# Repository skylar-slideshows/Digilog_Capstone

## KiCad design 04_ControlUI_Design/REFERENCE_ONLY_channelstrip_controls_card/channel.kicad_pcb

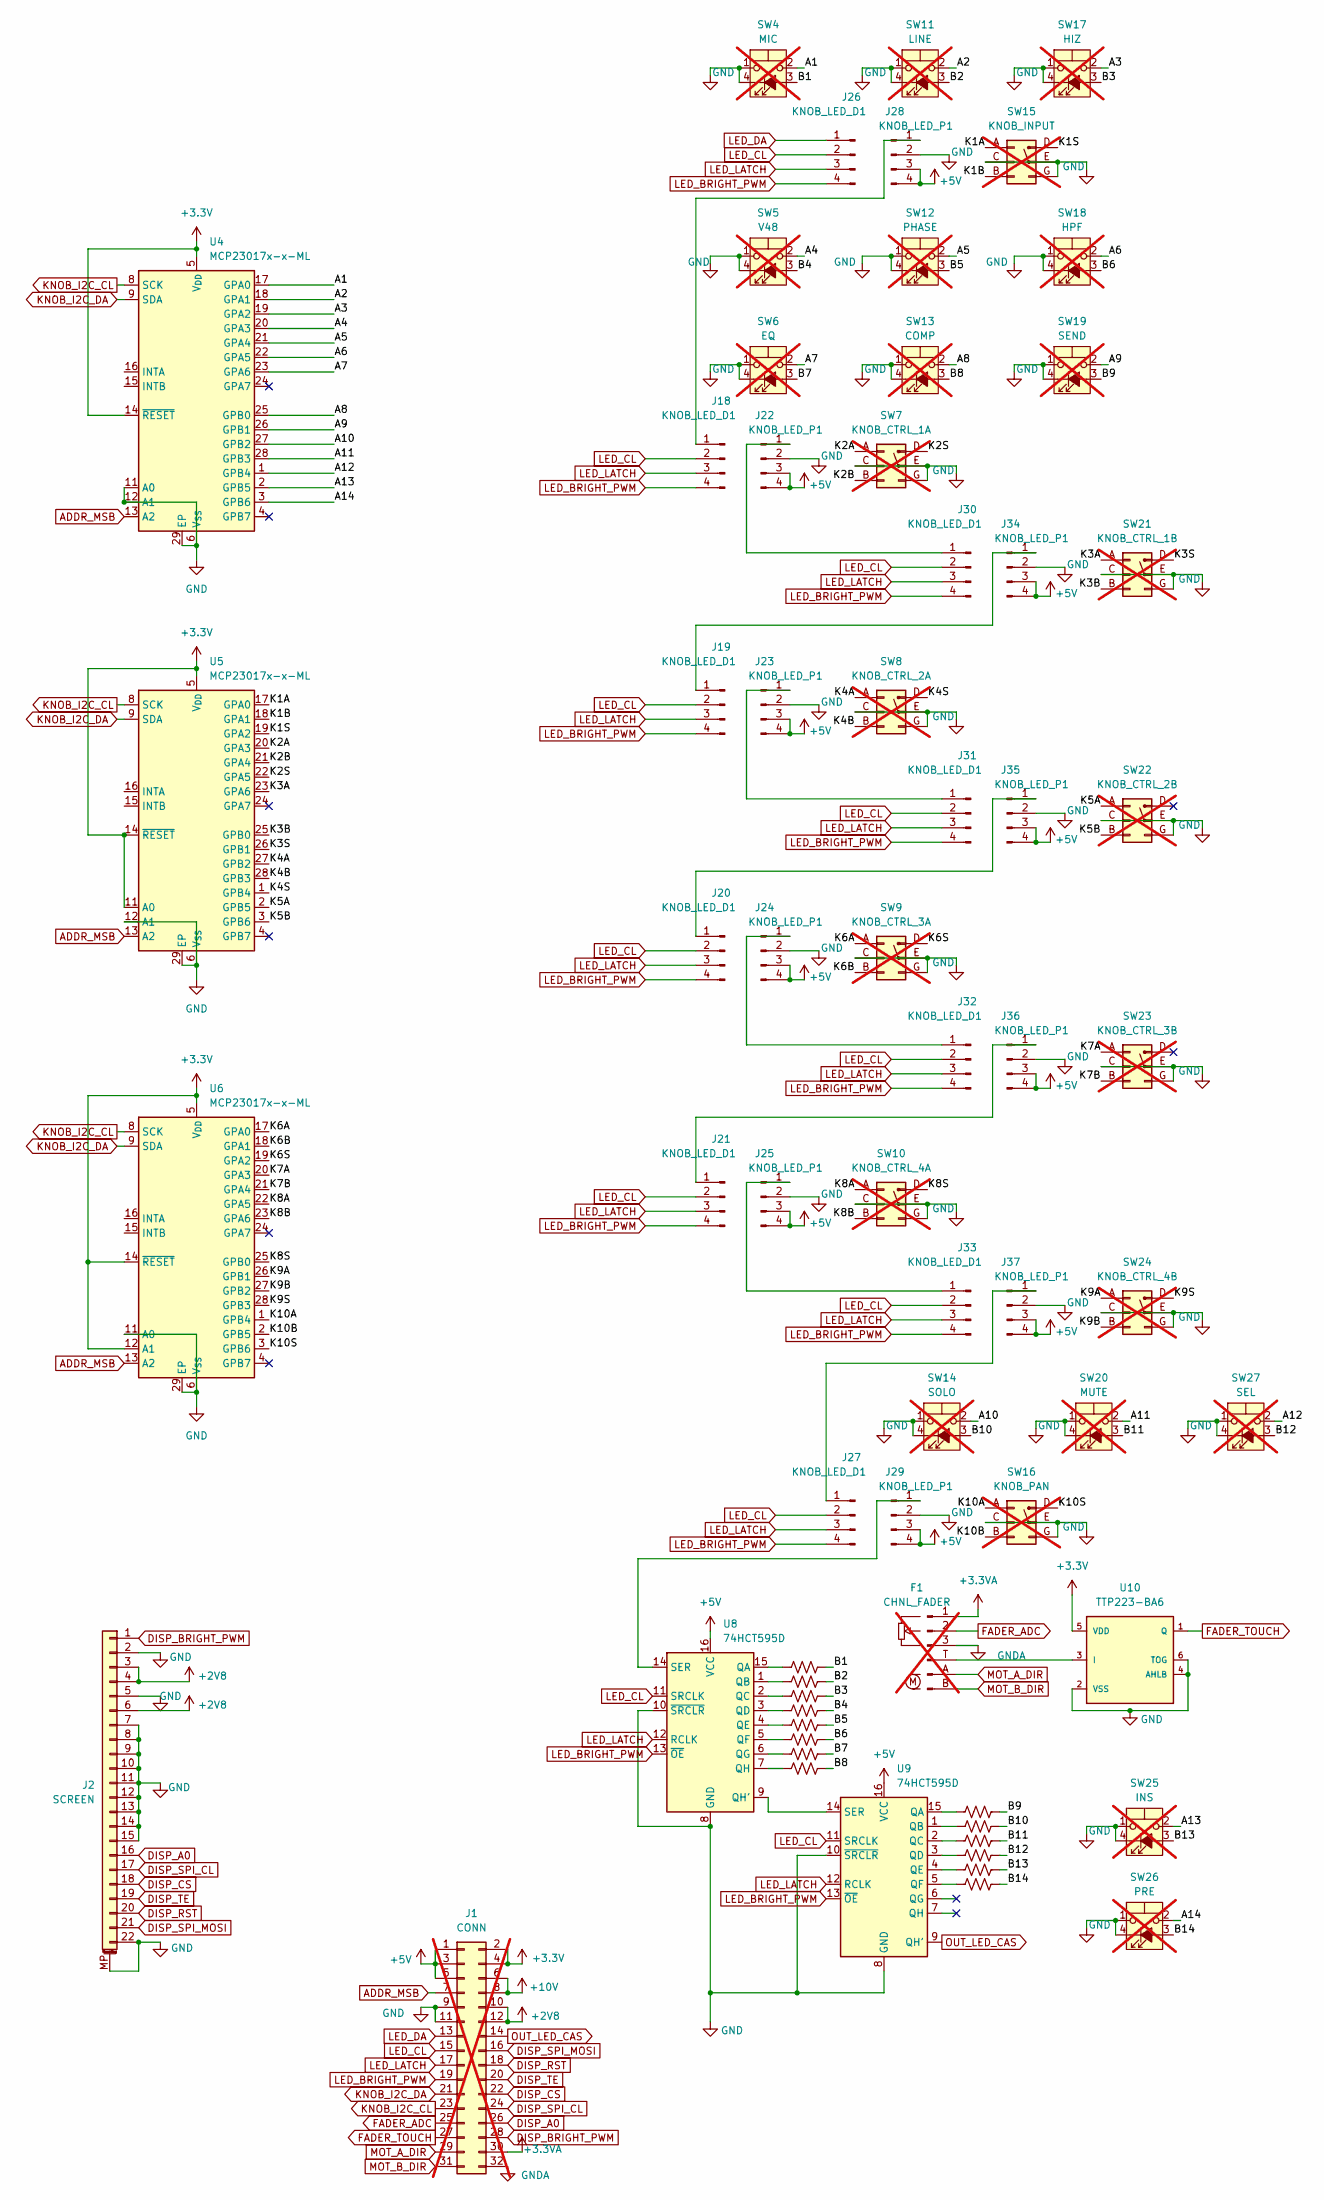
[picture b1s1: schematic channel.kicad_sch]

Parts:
F1: CHNL_FADER; TRIM_RSA0N11M9A07; not fitted
J1: CONN; PinHeader_2x16_P2.54mm_Vertical; not fitted
J2: SCREEN; TE_2-1734839-2_1x22-1MP_P0.5mm_Horizontal; LCSC C22435644
J18, J19, J20, J21, J26, J27, J30, J31, J32, J33: KNOB_LED_D1; PinSocket_1x04_P2.54mm_Vertical; LCSC C2718488
J22, J23, J24, J25, J28, J29, J34, J35, J36, J37: KNOB_LED_P1; PinSocket_1x04_P2.54mm_Vertical; LCSC C2718488
R1, R2, R3, R4, R5, R6, R7, R8, R9, R10, R11, R12, R13, R14: 330; R_0603_1608Metric; LCSC C25231
SW4: MIC; CFPB-1CC-4W6; not fitted
SW5: V48; CFPB-1CC-4W6; not fitted
SW6: EQ; CFPB-1CC-4W6; not fitted
SW7: KNOB_CTRL_1A; EC11J0924411; not fitted
SW8: KNOB_CTRL_2A; EC11J0924411; not fitted
SW9: KNOB_CTRL_3A; EC11J0924411; not fitted
SW10: KNOB_CTRL_4A; EC11J0924411; not fitted
SW11: LINE; CFPB-1CC-4W6; not fitted
SW12: PHASE; CFPB-1CC-4W6; not fitted
SW13: COMP; CFPB-1CC-4W6; not fitted
SW14: SOLO; CFPB-1CC-4W6; not fitted
SW15: KNOB_INPUT; EC11J0924411; not fitted
SW16: KNOB_PAN; EC11J0924411; not fitted
SW17: HIZ; CFPB-1CC-4W6; not fitted
SW18: HPF; CFPB-1CC-4W6; not fitted
SW19: SEND; CFPB-1CC-4W6; not fitted
SW20: MUTE; CFPB-1CC-4W6; not fitted
SW21: KNOB_CTRL_1B; EC11J0924411; not fitted
SW22: KNOB_CTRL_2B; EC11J0924411; not fitted
SW23: KNOB_CTRL_3B; EC11J0924411; not fitted
SW24: KNOB_CTRL_4B; EC11J0924411; not fitted
SW25: INS; CFPB-1CC-4W6; not fitted
SW26: PRE; CFPB-1CC-4W6; not fitted
SW27: SEL; CFPB-1CC-4W6; not fitted
U4, U5, U6: MCP23017x-x-ML; QFN-28-1EP_6x6mm_P0.65mm_EP4.25x4.25mm_ThermalVias; LCSC C629439
U8, U9: 74HCT595D; JEITA_SOIC-16_3.9x9.9mm_P1.27mm; LCSC C52140404
U10: TTP223-BA6; SOT-23-6; LCSC C42422127

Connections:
+2V8: J1.10, J1.12, J2.3, J2.4, J2.6
+3.3V: J1.2, J1.4, U4.5 (V_{DD}), U4.14 (~RESET), U5.5 (V_{DD}), U5.11 (A0), U5.14 (~RESET), U6.5 (V_{DD}), U6.12 (A1), U6.14 (~RESET), U10.5 (VDD)
+3.3VA: F1.1, J1.30
+5V: J1.1, J1.3, J1.5, J22.3, J22.4, J23.3, J23.4, J24.3, J24.4, J25.3, J25.4, J28.3, J28.4, J29.3, J29.4, J34.3, J34.4, J35.3, J35.4, J36.3, J36.4, J37.3, J37.4, U8.16 (VCC), U9.16 (VCC)
+10V: J1.6, J1.8
/A1: SW4.2, U4.17 (GPA0)
/A2: SW11.2, U4.18 (GPA1)
/A3: SW17.2, U4.19 (GPA2)
/A4: SW5.2, U4.20 (GPA3)
/A5: SW12.2, U4.21 (GPA4)
/A6: SW18.2, U4.22 (GPA5)
/A7: SW6.2, U4.23 (GPA6)
/A8: SW13.2, U4.25 (GPB0)
/A9: SW19.2, U4.26 (GPB1)
/A10: SW14.2, U4.27 (GPB2)
/A11: SW20.2, U4.28 (GPB3)
/A12: SW27.2, U4.1 (GPB4)
/A13: SW25.2, U4.2 (GPB5)
/A14: SW26.2, U4.3 (GPB6)
/B1: R1.2, SW4.3 (A)
/B2: R2.2, SW11.3 (A)
/B3: R3.2, SW17.3 (A)
/B4: R4.2, SW5.3 (A)
/B5: R5.2, SW12.3 (A)
/B6: R6.2, SW18.3 (A)
/B7: R7.2, SW6.3 (A)
/B8: R8.2, SW13.3 (A)
/B9: R9.2, SW19.3 (A)
/B10: R10.2, SW14.3 (A)
/B11: R11.2, SW20.3 (A)
/B12: R12.2, SW27.3 (A)
/B13: R13.2, SW25.3 (A)
/B14: R14.2, SW26.3 (A)
/K1A: SW15.A (Pin_1), U5.17 (GPA0)
/K1B: SW15.B (Pin_3), U5.18 (GPA1)
/K1S: SW15.D (Pin_4), U5.19 (GPA2)
/K2A: SW7.A (Pin_1), U5.20 (GPA3)
/K2B: SW7.B (Pin_3), U5.21 (GPA4)
/K2S: SW7.D (Pin_4), U5.22 (GPA5)
/K3A: SW21.A (Pin_1), U5.23 (GPA6)
/K3B: SW21.B (Pin_3), U5.25 (GPB0)
/K3S: SW21.D (Pin_4), U5.26 (GPB1)
/K4A: SW8.A (Pin_1), U5.27 (GPB2)
/K4B: SW8.B (Pin_3), U5.28 (GPB3)
/K4S: SW8.D (Pin_4), U5.1 (GPB4)
/K5A: SW22.A (Pin_1), U5.2 (GPB5)
/K5B: SW22.B (Pin_3), U5.3 (GPB6)
/K6A: SW9.A (Pin_1), U6.17 (GPA0)
/K6B: SW9.B (Pin_3), U6.18 (GPA1)
/K6S: SW9.D (Pin_4), U6.19 (GPA2)
/K7A: SW23.A (Pin_1), U6.20 (GPA3)
/K7B: SW23.B (Pin_3), U6.21 (GPA4)
/K8A: SW10.A (Pin_1), U6.22 (GPA5)
/K8B: SW10.B (Pin_3), U6.23 (GPA6)
/K8S: SW10.D (Pin_4), U6.25 (GPB0)
/K9A: SW24.A (Pin_1), U6.26 (GPB1)
/K9B: SW24.B (Pin_3), U6.27 (GPB2)
/K9S: SW24.D (Pin_4), U6.28 (GPB3)
/K10A: SW16.A (Pin_1), U6.1 (GPB4)
/K10B: SW16.B (Pin_3), U6.2 (GPB5)
/K10S: SW16.D (Pin_4), U6.3 (GPB6)
ADDR_MSB: J1.7, U4.13 (A2), U5.13 (A2), U6.13 (A2)
DISP_A0: J1.26, J2.16
DISP_BRIGHT_PWM: J1.28, J2.1
DISP_CS: J1.22, J2.18
DISP_RST: J1.18, J2.20
DISP_SPI_CL: J1.24, J2.17
DISP_SPI_MOSI: J1.16, J2.21
DISP_TE: J1.20, J2.19
FADER_ADC: F1.2, J1.25
FADER_TOUCH: J1.27, U10.1 (Q)
GND: J1.9, J1.11, J2.2, J2.5, J2.7, J2.8, J2.9, J2.10, J2.11, J2.12, J2.13, J2.14, J2.15, J2.22, J2.MP (MountPin), J22.2, J23.2, J24.2, J25.2, J28.2, J29.2, J34.2, J35.2, J36.2, J37.2, SW4.1, SW4.4 (K), SW5.1, SW5.4 (K), SW6.1, SW6.4 (K), SW7.C (Pin_2), SW7.E (Pin_5), SW7.G (Pin_6), SW8.C (Pin_2), SW8.E (Pin_5), SW8.G (Pin_6), SW9.C (Pin_2), SW9.E (Pin_5), SW9.G (Pin_6), SW10.C (Pin_2), SW10.E (Pin_5), SW10.G (Pin_6), SW11.1, SW11.4 (K), SW12.1, SW12.4 (K), SW13.1, SW13.4 (K), SW14.1, SW14.4 (K), SW15.C (Pin_2), SW15.E (Pin_5), SW15.G (Pin_6), SW16.C (Pin_2), SW16.E (Pin_5), SW16.G (Pin_6), SW17.1, SW17.4 (K), SW18.1, SW18.4 (K), SW19.1, SW19.4 (K), SW20.1, SW20.4 (K), SW21.C (Pin_2), SW21.E (Pin_5), SW21.G (Pin_6), SW22.C (Pin_2), SW22.E (Pin_5), SW22.G (Pin_6), SW23.C (Pin_2), SW23.E (Pin_5), SW23.G (Pin_6), SW24.C (Pin_2), SW24.E (Pin_5), SW24.G (Pin_6), SW25.1, SW25.4 (K), SW26.1, SW26.4 (K), SW27.1, SW27.4 (K), U4.6 (V_{SS}), U4.11 (A0), U4.12 (A1), U4.29 (EP), U5.6 (V_{SS}), U5.12 (A1), U5.29 (EP), U6.6 (V_{SS}), U6.11 (A0), U6.29 (EP), U8.8 (GND), U8.10 (~SRCLR), U9.8 (GND), U9.10 (~SRCLR), U10.2 (VSS), U10.4 (AHLB), U10.6 (TOG)
GNDA: F1.3, J1.32
KNOB_I2C_CL: J1.23, U4.8 (SCK), U5.8 (SCK), U6.8 (SCK)
KNOB_I2C_DA: J1.21, U4.9 (SDA), U5.9 (SDA), U6.9 (SDA)
LED_BRIGHT_PWM: J1.19, J18.4, J19.4, J20.4, J21.4, J26.4, J27.4, J30.4, J31.4, J32.4, J33.4, U8.13 (~OE), U9.13 (~OE)
LED_CL: J1.15, J18.2, J19.2, J20.2, J21.2, J26.2, J27.2, J30.2, J31.2, J32.2, J33.2, U8.11 (SRCLK), U9.11 (SRCLK)
LED_DA: J1.13, J26.1
LED_LATCH: J1.17, J18.3, J19.3, J20.3, J21.3, J26.3, J27.3, J30.3, J31.3, J32.3, J33.3, U8.12 (RCLK), U9.12 (RCLK)
MOT_A_DIR: F1.A (Pin_5), J1.29
MOT_B_DIR: F1.B (Pin_6), J1.31
unnamed: F1.T (Pin_4), U10.3 (I)
unnamed: J18.1, J28.1
unnamed: J19.1, J34.1
unnamed: J20.1, J35.1
unnamed: J21.1, J36.1
unnamed: J22.1, J30.1
unnamed: J23.1, J31.1
unnamed: J24.1, J32.1
unnamed: J25.1, J33.1
unnamed: J27.1, J37.1
unnamed: J29.1, U8.14 (SER)
unnamed: R1.1, U8.15 (QA)
unnamed: R2.1, U8.1 (QB)
unnamed: R3.1, U8.2 (QC)
unnamed: R4.1, U8.3 (QD)
unnamed: R5.1, U8.4 (QE)
unnamed: R6.1, U8.5 (QF)
unnamed: R7.1, U8.6 (QG)
unnamed: U8.9 (QH'), U9.14 (SER)
unnamed: R8.1, U8.7 (QH)
unnamed: R9.1, U9.15 (QA)
unnamed: R10.1, U9.1 (QB)
unnamed: R11.1, U9.2 (QC)
unnamed: R12.1, U9.3 (QD)
unnamed: R13.1, U9.4 (QE)
unnamed: R14.1, U9.5 (QF)
OUT_LED_CAS: J1.14, U9.9 (QH')

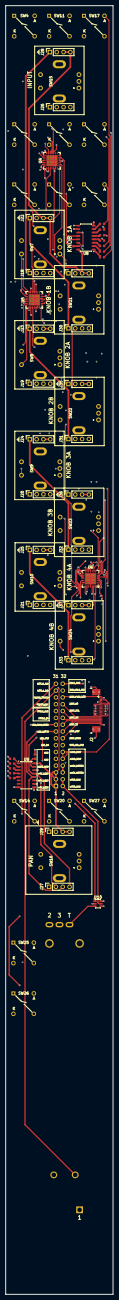
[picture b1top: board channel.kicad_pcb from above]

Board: 4 copper layers, 40.0 x 480.0 mm, 67 parts (1 on the bottom side), 108 nets.

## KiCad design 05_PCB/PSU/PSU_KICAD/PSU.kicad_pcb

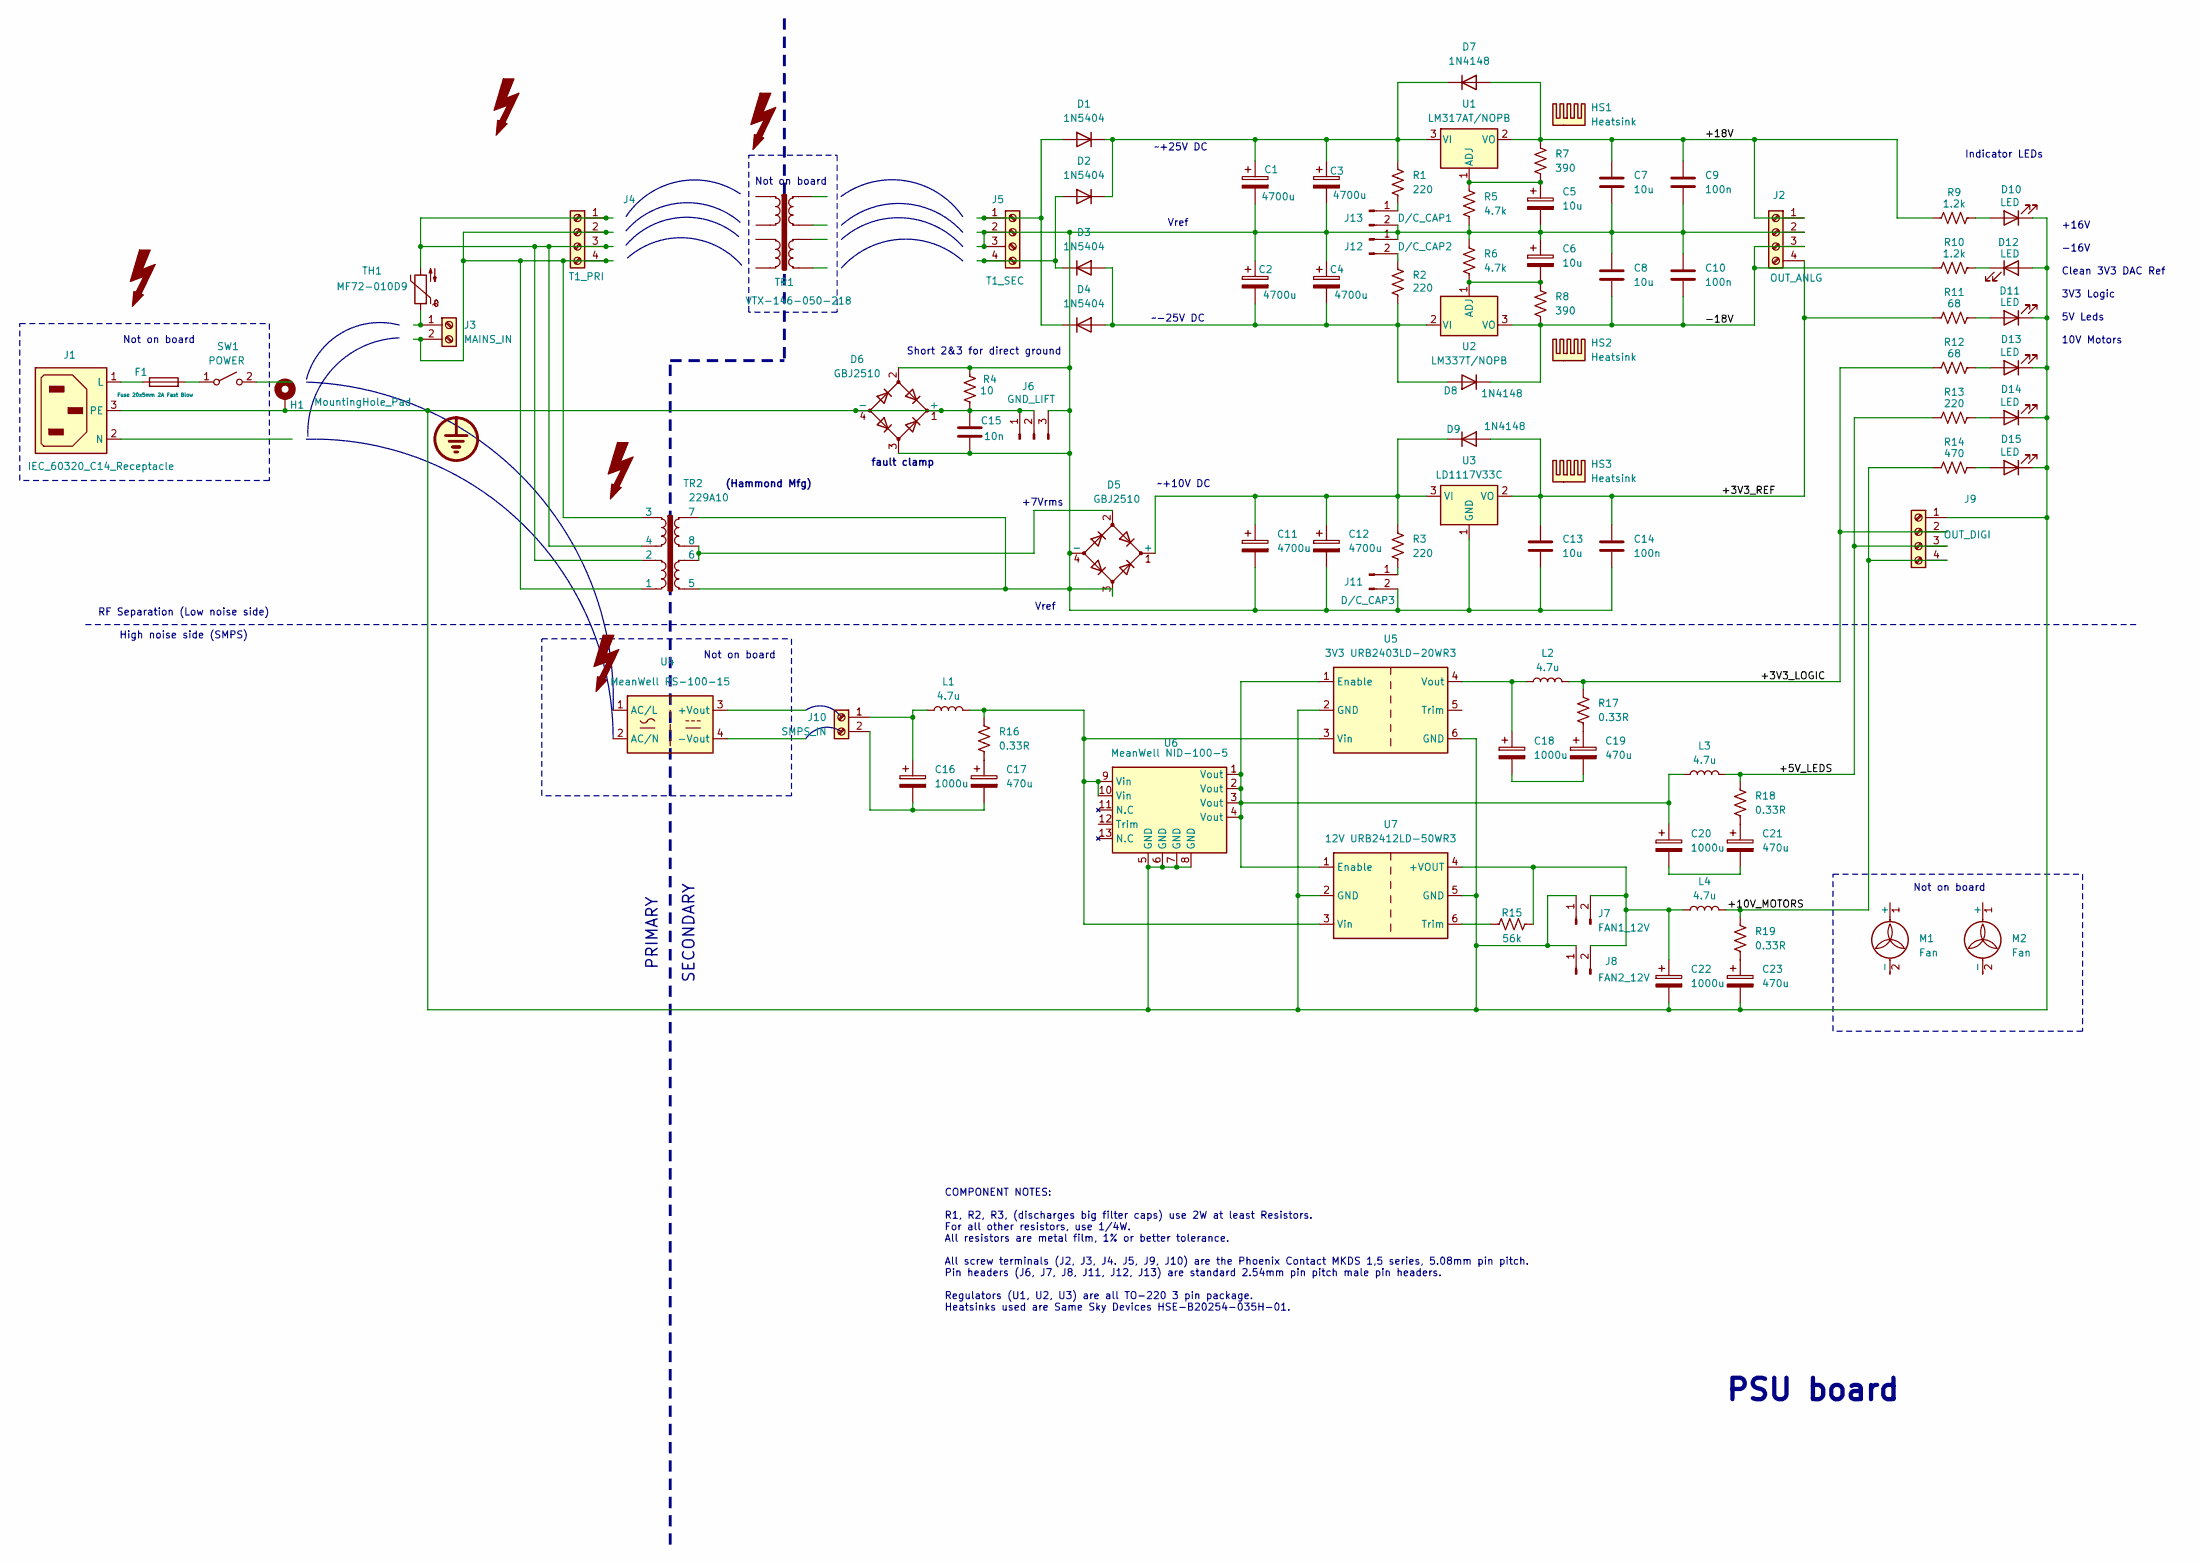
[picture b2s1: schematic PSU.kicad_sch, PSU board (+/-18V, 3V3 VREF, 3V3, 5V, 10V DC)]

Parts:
C1, C2, C3, C4, C11, C12: 4700u; CP_Radial_D18.0mm_P7.50mm; LCSC C443892
C5, C6: 10u; CP_Elec_6.3x5.4; LCSC C14162
C7, C8, C13: 10u; C_Rect_L24.0mm_W12.6mm_P22.50mm_MKT; LCSC C328801
C9, C10, C14: 100n; C_1206_3216Metric; LCSC C1945
C15: 10n; C_1206_3216Metric; LCSC C55077
C16, C18, C20, C22: 1000u; CP_Radial_D12.5mm_P5.00mm; LCSC C122661
C17, C19, C21, C23: 470u; CP_Radial_D10.0mm_P5.00mm; LCSC C116237
D1, D2, D3, D4: 1N5404; D_DO-201AD_P15.24mm_Horizontal; LCSC C222547
D5, D6: GBJ2510; Diode_Bridge_32.0x5.6x17.0mm_P10.0mm_P7.5mm; LCSC C27523
D7, D8, D9: 1N4148; D_SOD-123; LCSC C2099
D10, D11, D12, D13, D14, D15: LED; LED_Rectangular_W3.9mm_H1.8mm
F1: Fuse 20x5mm 2A Fast Blow
H1: MountingHole_Pad; MountingHole_3.2mm_M3_Pad_TopBottom
HS1, HS2, HS3: Heatsink; HSINK_HSE-B20380-040H
J1: IEC_60320_C14_Receptacle
J2: OUT_ANLG; TerminalBlock_Phoenix_MKDS-1,5-4-5.08_1x04_P5.08mm_Horizont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; LCSC C5443561
J3: MAINS_IN; TerminalBlock_Phoenix_MKDS-1,5-2-5.08_1x02_P5.08mm_Horizont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; LCSC C5443539
J4: T1_PRI; TerminalBlock_Phoenix_MKDS-1,5-4-5.08_1x04_P5.08mm_Horizont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; LCSC C5443561
J5: T1_SEC; TerminalBlock_Phoenix_MKDS-1,5-4-5.08_1x04_P5.08mm_Horizont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; LCSC C5443561
J6: GND_LIFT; PinHeader_1x03_P2.54mm_Vertical; LCSC C5360899
J7: FAN1_12V; PinHeader_1x02_P2.54mm_Vertical; LCSC C5360898
J8: FAN2_12V; PinHeader_1x02_P2.54mm_Vertical; LCSC C5360898
J9: OUT_DIGI; TerminalBlock_Phoenix_MKDS-1,5-4-5.08_1x04_P5.08mm_Horizont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; LCSC C5443561
J10: SMPS_IN; TerminalBlock_Phoenix_MKDS-1,5-2-5.08_1x02_P5.08mm_Horizont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; LCSC C5443539
J11: D/C_CAP3; PinHeader_1x02_P2.54mm_Vertical
J12: D/C_CAP2; PinHeader_1x02_P2.54mm_Vertical
J13: D/C_CAP1; PinHeader_1x02_P2.54mm_Vertical
L1, L2, L3, L4: 4.7u; L_Vishay_IHLP-5050; LCSC C845092
M1, M2: Fan
R1, R2, R3: 220; R_Axial_DIN0414_L11.9mm_D4.5mm_P20.32mm_Horizontal; LCSC C5200473
R4: 10; R_0805_2012Metric; LCSC C340448
R5, R6: 4.7k; R_1206_3216Metric; LCSC C702850
R7, R8: 390; R_1206_3216Metric; LCSC C497314
R9, R10: 1.2k; R_1206_3216Metric; LCSC C17891
R11, R12: 68; R_1206_3216Metric; LCSC C294793
R13: 220; R_1206_3216Metric; LCSC C25363
R14: 470; R_1206_3216Metric; LCSC C25383
R15: 56k; R_1206_3216Metric; LCSC C4513
R16, R17, R18, R19: 0.33R; R_Axial_DIN0207_L6.3mm_D2.5mm_P10.16mm_Horizontal; LCSC C119970
SW1: POWER
TH1: MF72-010D9; C_Disc_D12.5mm_W5.0mm_P7.50mm
TR1: VTX-146-050-218
TR2: 229A10
U1: LM317AT/NOPB; TO-220-3_Vertical; LCSC C94659
U2: LM337T/NOPB; TO-220-3_Vertical; LCSC C2869423
U3: LD1117V33C; TO-220-3_Vertical; LCSC C672117
U4: MeanWell RS-100-15
U5: 3V3 URB2403LD-20WR3; Converter_DCDC_XP_POWER_JTDxxxxxxx_THT
U6: MeanWell NID-100-5; MeanWell NID100
U7: 12V URB2412LD-50WR3; urb 50w dc-dc

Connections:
/+3V3_LOGIC: J9.2, L2.2, R12.1, R17.1
/+3V3_REF: C13.1, C14.1, D9.2 (A), J2.4, R11.1, U3.2 (VO)
/+5V_LEDS: J9.3, L3.2, R13.1, R18.1
/+10V_MOTORS: J9.4, L4.2, R14.1, R19.1
/+18V: C7.1, C9.1, D7.2 (A), J2.1, R7.1, R9.1, U1.2 (VO)
/-18V: C8.2, C10.2, D8.1 (K), J2.3, R8.2, R10.1, U2.3 (VO)
unnamed: C17.1, R16.2
unnamed: C18.2, C19.2
unnamed: C19.1, R17.2
unnamed: C20.2, C21.2
unnamed: C21.1, R18.2
unnamed: C23.1, R19.2
unnamed: D1.2 (A), D4.1 (K), J5.1
unnamed: C1.1, C3.1, D1.1 (K), D2.1 (K), D7.1 (K), R1.1, U1.3 (VI)
unnamed: D2.2 (A), D3.1 (K), J5.4
unnamed: C2.2, C4.2, D3.2 (A), D4.2 (A), D8.2 (A), R2.2, U2.2 (VI)
unnamed: C11.1, C12.1, D5.1 (+), D9.1 (K), R3.1, U3.3 (VI)
unnamed: C1.2, C2.1, C3.2, C4.1, C5.2, C6.1, C7.2, C8.1, C9.2, C10.1, C11.2, C12.2, C13.2, C14.2, C15.1, D5.3, D5.4 (-), D6.2, D6.3, J2.2, J5.2, J5.3, J6.3, J11.2, J12.1, J13.2, R4.2, R5.2, R6.1, TR2.5, TR2.7, U3.1 (GND)
unnamed: D5.2, TR2.6, TR2.8
unnamed: D10.2 (A), R9.2
unnamed: C15.2, C22.2, C23.2, D6.1 (+), D6.4 (-), D10.1 (K), D11.2 (A), D12.1 (K), D13.1 (K), D14.1 (K), D15.1 (K), H1.1 (1_1), J1.3 (PE), J6.1, J6.2, J7.1, J8.1, J9.1, R4.1, U5.2 (GND), U5.6 (GND), U6.5 (GND), U6.6 (GND), U6.7 (GND), U6.8 (GND), U7.2 (GND), U7.5 (GND)
unnamed: D11.1 (K), R10.2
unnamed: D12.2 (A), R11.2
unnamed: D13.2 (A), R12.2
unnamed: D14.2 (A), R13.2
unnamed: D15.2 (A), R14.2
unnamed: F1.1, J1.1 (L)
unnamed: F1.2, SW1.1 (A)
unnamed: J3.1, TH1.1
unnamed: J3.2, J4.2, J4.4, TR2.1, TR2.3
unnamed: J4.1, J4.3, TH1.2, TR2.2, TR2.4
unnamed: C22.1, J7.2, J8.2, L4.1, R15.2, U7.4 (+VOUT)
unnamed: C16.1, J10.1, L1.1
unnamed: C16.2, C17.2, J10.2
unnamed: J11.1, R3.2
unnamed: J12.2, R2.1
unnamed: J13.1, R1.2
unnamed: C5.1, R5.1, R7.2, U1.1 (ADJ)
unnamed: C6.2, R6.2, R8.1, U2.1 (ADJ)
unnamed: C20.1, L3.1, U5.1 (Enable), U6.1 (Vout), U6.2 (Vout), U6.3 (Vout), U6.4 (Vout), U7.1 (Enable)
unnamed: L1.2, R16.1, U5.3 (Vin), U6.9 (Vin), U6.10 (Vin), U7.3 (Vin)
unnamed: C18.1, L2.1, U5.4 (Vout)
unnamed: R15.1, U7.6 (Trim)

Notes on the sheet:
Indicator LEDs
COMPONENT NOTES: R1, R2, R3, (discharges big filter caps) use 2W at least Resistors. For all other resistors, use 1/4W. All resistors are metal film, 1% or better tolerance. All screw terminals (J2, J3, J4. J5, J9, J10) are the Phoenix Contact MKDS 1,5 series, 5.08mm pin pitch. Pin headers (J6, J7,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
Vref
fault clamp
Short 2&3 for direct ground
+7Vrms
~-25V DC
Not on board
~+10V DC
~+25V DC
+16V -16V Clean 3V3 DAC Ref 3V3 Logic 5V Leds 10V Motors
PSU board
(Hammond Mfg)
PRIMARY SECONDARY
RF Separation (Low noise side) High noise side (SMPS)

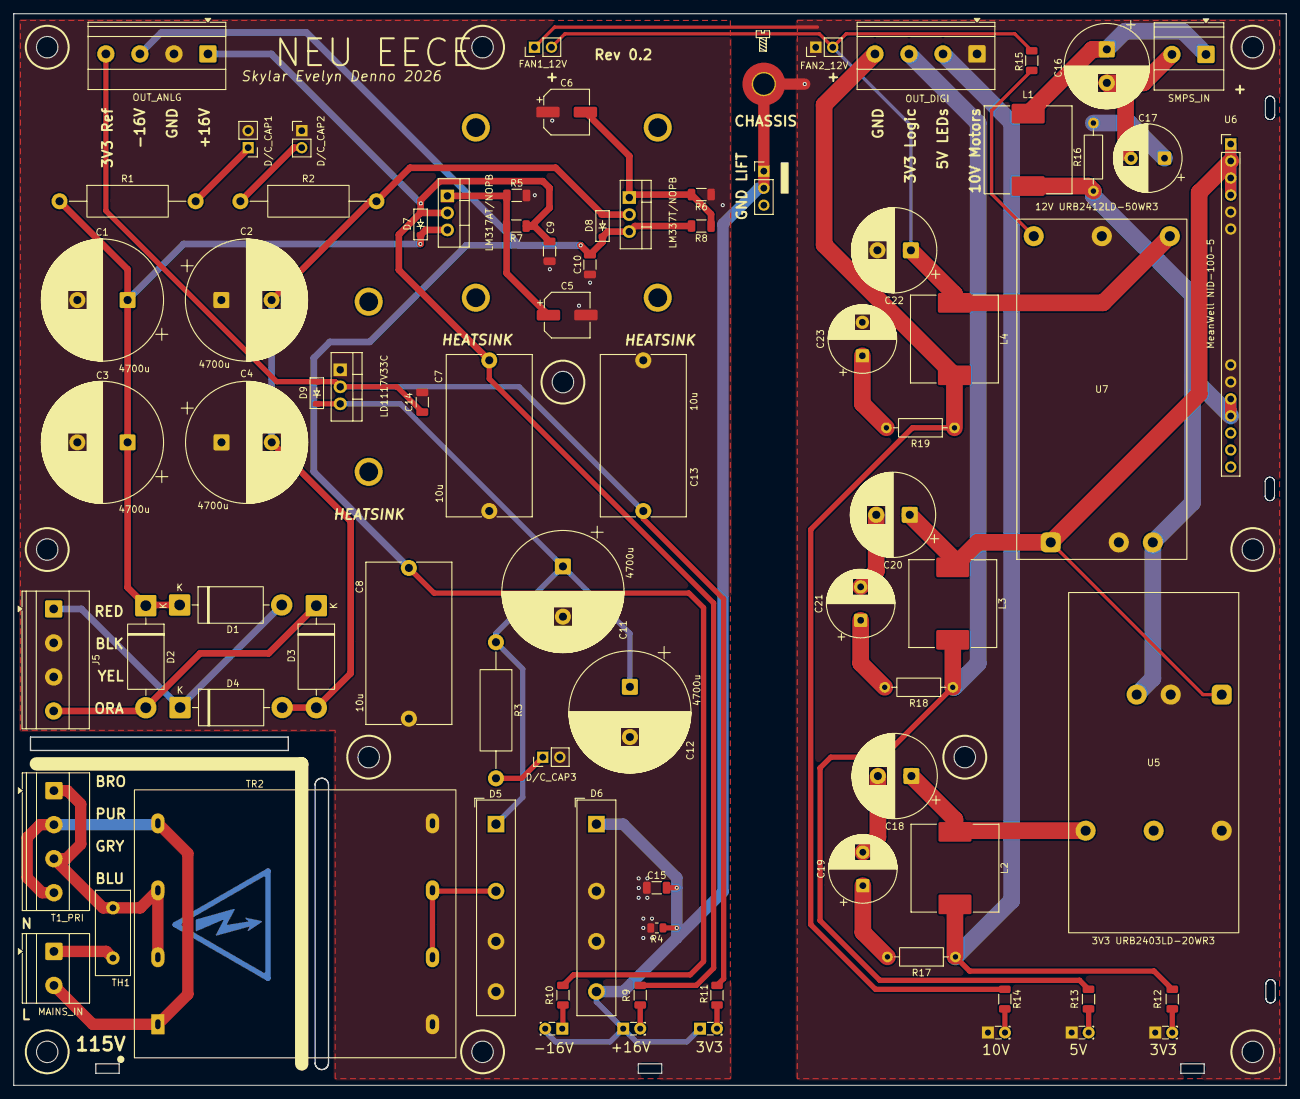
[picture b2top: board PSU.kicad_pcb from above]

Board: 4 copper layers, 190.0 x 160.0 mm, 85 parts (0 on the bottom side), 41 nets.

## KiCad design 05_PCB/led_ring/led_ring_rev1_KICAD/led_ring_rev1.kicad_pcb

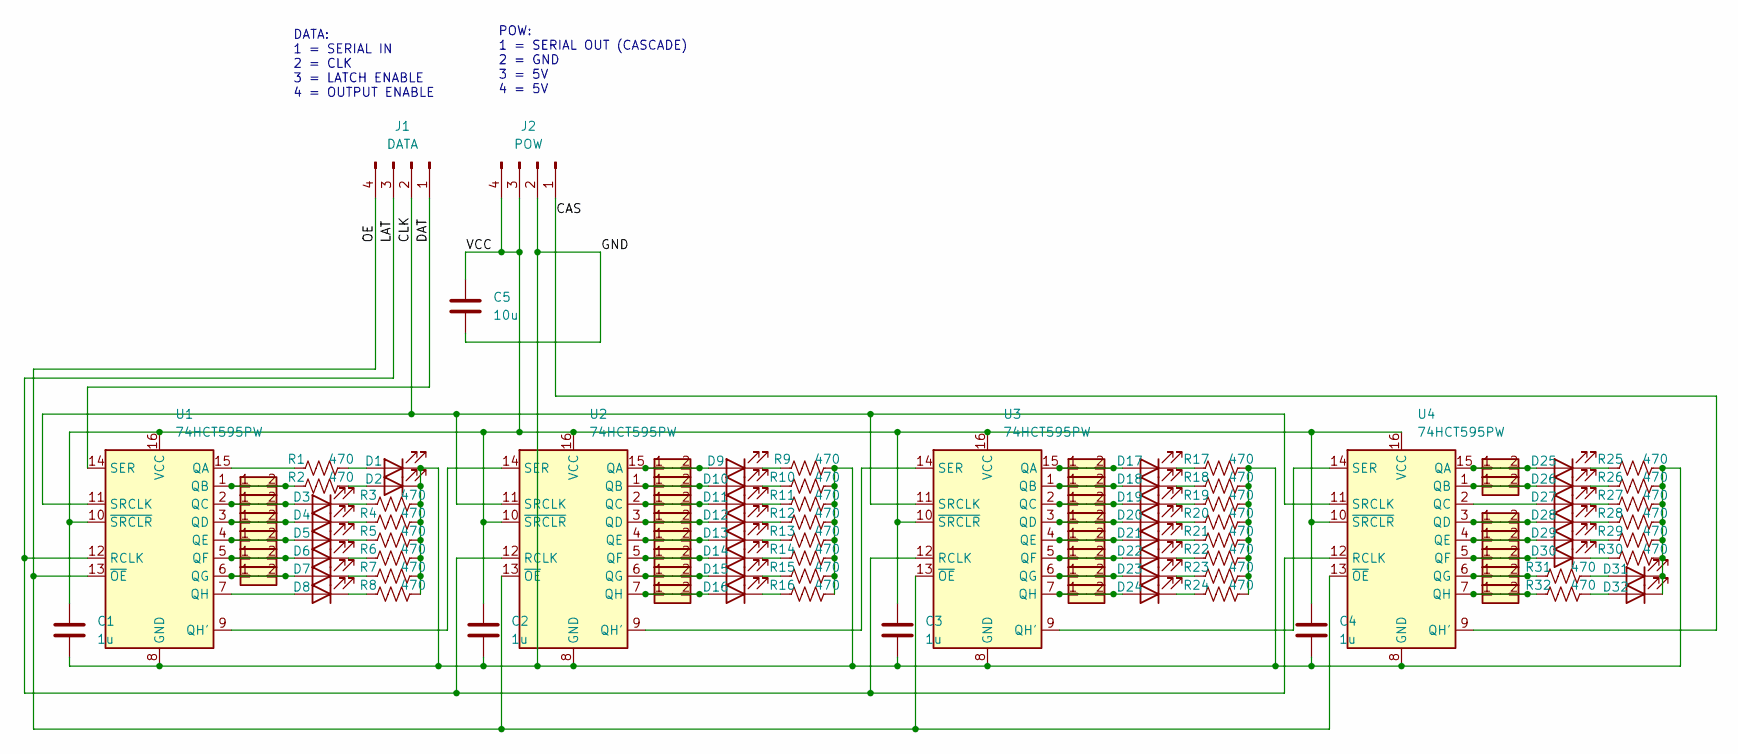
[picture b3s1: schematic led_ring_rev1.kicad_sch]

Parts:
C1, C2, C3, C4: 1u; C_0402_1005Metric; LCSC C14445
C5: 10u; C_0402_1005Metric; LCSC C15525
D1, D2, D3, D4, D5, D6, D7, D8, D9, D10, D11, D12, D13, D14, D15, D16, D17, D18, D19, D20, D21, D22, D23, D24, D25, D26, D27, D28, D29, D30, D31, D32: LED; LED_0201_0603Metric_shift; LCSC C52675959
J1: DATA; PinHeader_1x04_P2.54mm_Vertical; LCSC C5116483
J2: POW; PinHeader_1x04_P2.54mm_Vertical; LCSC C5116483
R1, R2, R3, R4, R5, R6, R7, R8, R9, R10, R11, R12, R13, R14, R15, R16, R17, R18, R19, R20, R21, R22, R23, R24, R25, R26, R27, R28, R29, R30, R31, R32: 470; R_0201_0603Metric; LCSC C295802
U1, U2, U3, U4: 74HCT595PW; TSSOP-16_4.4x5mm_P0.65mm; LCSC C54411086
V2, V3, V4, V5, V6, V7, V9, V10, V11, V12, V13, V14, V15, V16, V17, V18, V19, V20, V21, V22, V23, V24, V25, V26, V28, V29, V30, V31, V32: VIA; VIA_0.5_0.3

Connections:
/CAS: J2.1, U4.9 (QH')
/CLK: J1.2, U1.11 (SRCLK), U2.11 (SRCLK), U3.11 (SRCLK), U4.11 (SRCLK)
/DAT: J1.1, U1.14 (SER)
/GND: C1.2, C2.2, C3.2, C4.2, C5.2, D1.1 (K), D2.1 (K), D31.1 (K), D32.1 (K), J2.2, R3.2, R4.2, R5.2, R6.2, R7.2, R8.2, R9.2, R10.2, R11.2, R12.2, R13.2, R14.2, R15.2, R16.2, R17.2, R18.2, R19.2, R20.2, R21.2, R22.2, R23.2, R24.2, R25.2, R26.2, R27.2, R28.2, R29.2, R30.2, U1.8 (GND), U2.8 (GND), U3.8 (GND), U4.8 (GND)
/LAT: J1.3, U1.12 (RCLK), U2.12 (RCLK), U3.12 (RCLK), U4.12 (RCLK)
/OE: J1.4, U1.13 (~OE), U2.13 (~OE), U3.13 (~OE), U4.13 (~OE)
/VCC: C1.1, C2.1, C3.1, C4.1, C5.1, J2.3, J2.4, U1.10 (~SRCLR), U1.16 (VCC), U2.10 (~SRCLR), U2.16 (VCC), U3.10 (~SRCLR), U3.16 (VCC), U4.10 (~SRCLR), U4.16 (VCC)
unnamed: D1.2 (A), R1.2
unnamed: D2.2 (A), R2.2
unnamed: D3.2 (A), U1.2 (QC), V3.1, V3.2
unnamed: D3.1 (K), R3.1
unnamed: D4.2 (A), U1.3 (QD), V4.1, V4.2
unnamed: D4.1 (K), R4.1
unnamed: D5.2 (A), U1.4 (QE), V5.1, V5.2
unnamed: D5.1 (K), R5.1
unnamed: D6.2 (A), U1.5 (QF), V6.1, V6.2
unnamed: D6.1 (K), R6.1
unnamed: D7.2 (A), U1.6 (QG), V7.1, V7.2
unnamed: D7.1 (K), R7.1
unnamed: D8.2 (A), U1.7 (QH)
unnamed: D8.1 (K), R8.1
unnamed: D9.2 (A), U2.15 (QA), V9.1, V9.2
unnamed: D9.1 (K), R9.1
unnamed: D10.2 (A), U2.1 (QB), V10.1, V10.2
unnamed: D10.1 (K), R10.1
unnamed: D11.2 (A), U2.2 (QC), V11.1, V11.2
unnamed: D11.1 (K), R11.1
unnamed: D12.2 (A), U2.3 (QD), V12.1, V12.2
unnamed: D12.1 (K), R12.1
unnamed: D13.2 (A), U2.4 (QE), V13.1, V13.2
unnamed: D13.1 (K), R13.1
unnamed: D14.2 (A), U2.5 (QF), V14.1, V14.2
unnamed: D14.1 (K), R14.1
unnamed: D15.2 (A), U2.6 (QG), V15.1, V15.2
unnamed: D15.1 (K), R15.1
unnamed: D16.2 (A), U2.7 (QH), V16.1, V16.2
unnamed: D16.1 (K), R16.1
unnamed: D17.2 (A), U3.15 (QA), V17.1, V17.2
unnamed: D17.1 (K), R17.1
unnamed: D18.2 (A), U3.1 (QB), V18.1, V18.2
unnamed: D18.1 (K), R18.1
unnamed: D19.2 (A), U3.2 (QC), V19.1, V19.2
unnamed: D19.1 (K), R19.1
unnamed: D20.2 (A), U3.3 (QD), V20.1, V20.2
unnamed: D20.1 (K), R20.1
unnamed: D21.2 (A), U3.4 (QE), V21.1, V21.2
unnamed: D21.1 (K), R21.1
unnamed: D22.2 (A), U3.5 (QF), V22.1, V22.2
unnamed: D22.1 (K), R22.1
unnamed: D23.2 (A), U3.6 (QG), V23.1, V23.2
unnamed: D23.1 (K), R23.1
unnamed: D24.2 (A), U3.7 (QH), V24.1, V24.2
unnamed: D24.1 (K), R24.1
unnamed: D25.2 (A), U4.15 (QA), V25.1, V25.2
unnamed: D25.1 (K), R25.1
unnamed: D26.2 (A), U4.1 (QB), V26.1, V26.2
unnamed: D26.1 (K), R26.1
unnamed: D27.2 (A), U4.2 (QC)
unnamed: D27.1 (K), R27.1
unnamed: D28.2 (A), U4.3 (QD), V28.1, V28.2
unnamed: D28.1 (K), R28.1
unnamed: D29.2 (A), U4.4 (QE), V29.1, V29.2
unnamed: D29.1 (K), R29.1
unnamed: D30.2 (A), U4.5 (QF), V30.1, V30.2
unnamed: D30.1 (K), R30.1
unnamed: D31.2 (A), R31.2
unnamed: D32.2 (A), R32.2
unnamed: R1.1, U1.15 (QA)
unnamed: R2.1, U1.1 (QB), V2.1, V2.2
unnamed: U1.9 (QH'), U2.14 (SER)
unnamed: U2.9 (QH'), U3.14 (SER)
unnamed: U3.9 (QH'), U4.14 (SER)
unnamed: R31.1, U4.6 (QG), V31.1, V31.2
unnamed: R32.1, U4.7 (QH), V32.1, V32.2

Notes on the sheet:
DATA: 1 = SERIAL IN 2 = CLK 3 = LATCH ENABLE 4 = OUTPUT ENABLE
POW: 1 = SERIAL OUT (CASCADE) 2 = GND 3 = 5V 4 = 5V

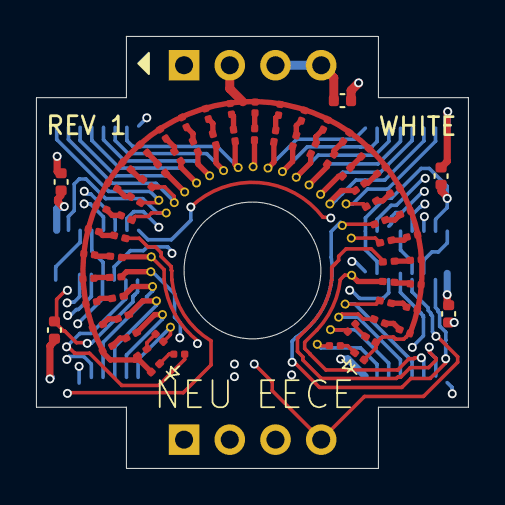
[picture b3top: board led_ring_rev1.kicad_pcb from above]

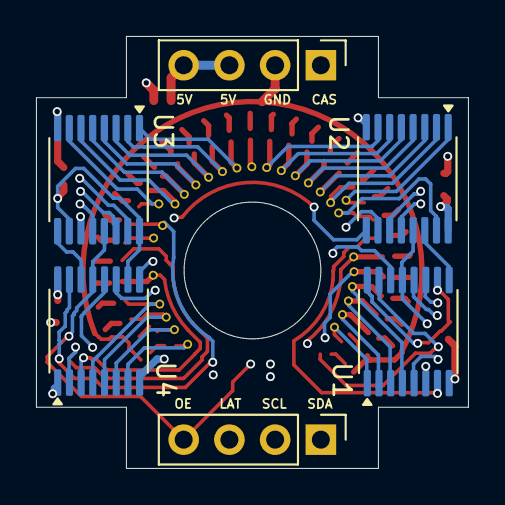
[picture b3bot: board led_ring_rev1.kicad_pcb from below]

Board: 4 copper layers, 24.0 x 24.0 mm, 104 parts (6 on the bottom side), 74 nets.

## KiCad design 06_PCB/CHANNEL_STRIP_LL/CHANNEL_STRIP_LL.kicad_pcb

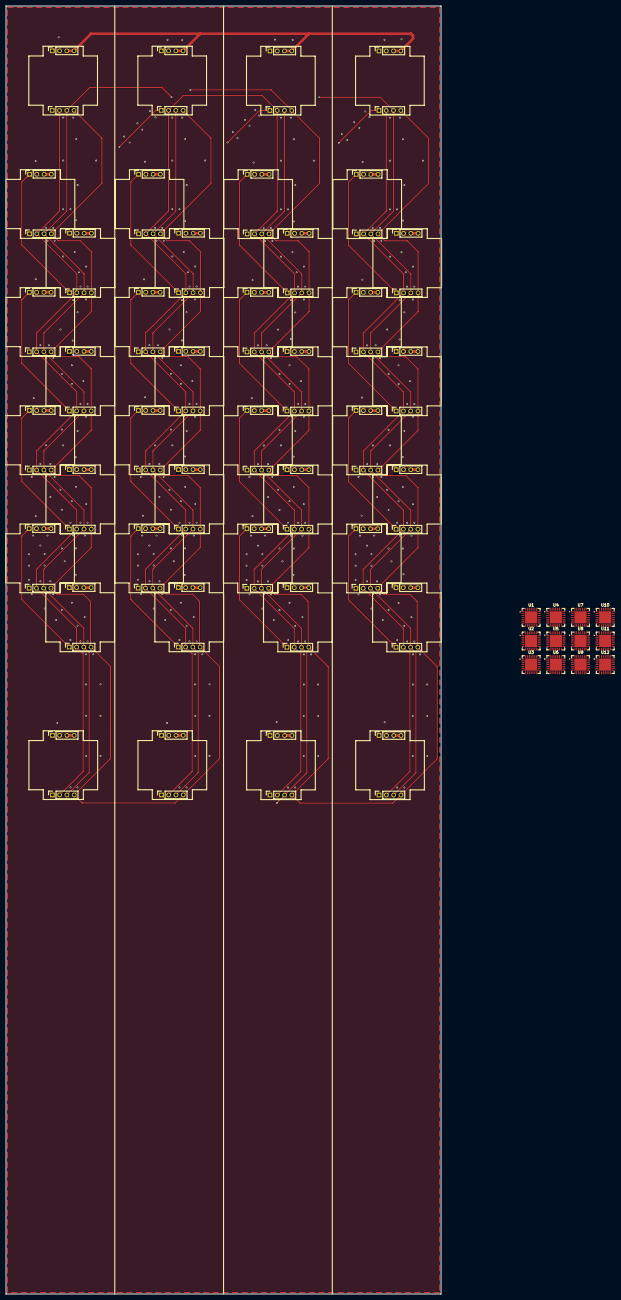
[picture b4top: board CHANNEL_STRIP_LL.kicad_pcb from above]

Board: 4 copper layers, 152.0 x 450.0 mm, 92 parts (0 on the bottom side), 45 nets.

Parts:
J1, J2, J3, J4, J5, J6, J7, J8, J9, J10, J11, J12, J13, J14, J15, J16, J17, J18, J19, J20, J21, J22, J23, J24, J25, J26, J27, J28, J29, J30, J31, J32, J33, J34, J35, J36, J37, J38, J39, J40, J41, J42, J43, J44, J45, J46, J47, J48, J49, J50, J51, J52, J53, J54, J55, J56, J57, J58, J59, J60, J61, J62, J63, J64, J65, J66, J67, J68, J69, J70, J71, J72, J73, J74, J75, J76, J77, J78, J79, J80: Conn_01x04_Socket; PinSocket_1x04_P2.54mm_Vertical
U1, U2, U3, U4, U5, U6, U7, U8, U9, U10, U11, U12: MCP23017x-x-ML; QFN-28-1EP_6x6mm_P0.65mm_EP4.25x4.25mm

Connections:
1_CAS_OUT: J20.1, J21.1
2_CAS_OUT: J40.1, J41.1
3_CAS_OUT: J60.1, J61.1
+3V3: U1.5 (V_{DD}), U1.11 (A0), U1.13 (A2), U1.14 (~RESET), U2.5 (V_{DD}), U2.12 (A1), U2.13 (A2), U2.14 (~RESET), U3.5 (V_{DD}), U3.11 (A0), U3.12 (A1), U3.13 (A2), U3.14 (~RESET), U4.5 (V_{DD}), U4.11 (A0), U4.13 (A2), U4.14 (~RESET), U5.5 (V_{DD}), U5.12 (A1), U5.13 (A2), U5.14 (~RESET), U6.5 (V_{DD}), U6.11 (A0), U6.12 (A1), U6.13 (A2), U6.14 (~RESET), U7.5 (V_{DD}), U7.11 (A0), U7.13 (A2), U7.14 (~RESET), U8.5 (V_{DD}), U8.12 (A1), U8.13 (A2), U8.14 (~RESET), U9.5 (V_{DD}), U9.11 (A0), U9.12 (A1), U9.13 (A2), U9.14 (~RESET), U10.5 (V_{DD}), U10.11 (A0), U10.13 (A2), U10.14 (~RESET), U11.5 (V_{DD}), U11.12 (A1), U11.13 (A2), U11.14 (~RESET), U12.5 (V_{DD}), U12.11 (A0), U12.12 (A1), U12.13 (A2), U12.14 (~RESET)
+5V: J2.3, J2.4, J4.3, J4.4, J6.3, J6.4, J8.3, J8.4, J10.3, J10.4, J12.3, J12.4, J14.3, J14.4, J16.3, J16.4, J18.3, J18.4, J20.3, J20.4, J22.3, J22.4, J24.3, J24.4, J26.3, J26.4, J28.3, J28.4, J30.3, J30.4, J32.3, J32.4, J34.3, J34.4, J36.3, J36.4, J38.3, J38.4, J40.3, J40.4, J42.3, J42.4, J44.3, J44.4, J46.3, J46.4, J48.3, J48.4, J50.3, J50.4, J52.3, J52.4, J54.3, J54.4, J56.3, J56.4, J58.3, J58.4, J60.3, J60.4, J62.3, J62.4, J64.3, J64.4, J66.3, J66.4, J68.3, J68.4, J70.3, J70.4, J72.3, J72.4, J74.3, J74.4, J76.3, J76.4, J78.3, J78.4, J80.3, J80.4
GND: J2.2, J4.2, J6.2, J8.2, J10.2, J12.2, J14.2, J16.2, J18.2, J20.2, J22.2, J24.2, J26.2, J28.2, J30.2, J32.2, J34.2, J36.2, J38.2, J40.2, J42.2, J44.2, J46.2, J48.2, J50.2, J52.2, J54.2, J56.2, J58.2, J60.2, J62.2, J64.2, J66.2, J68.2, J70.2, J72.2, J74.2, J76.2, J78.2, J80.2, U1.6 (V_{SS}), U1.12 (A1), U1.29 (EP), U2.6 (V_{SS}), U2.11 (A0), U2.29 (EP), U3.6 (V_{SS}), U3.29 (EP), U4.6 (V_{SS}), U4.12 (A1), U4.29 (EP), U5.6 (V_{SS}), U5.11 (A0), U5.29 (EP), U6.6 (V_{SS}), U6.29 (EP), U7.6 (V_{SS}), U7.12 (A1), U7.29 (EP), U8.6 (V_{SS}), U8.11 (A0), U8.29 (EP), U9.6 (V_{SS}), U9.29 (EP), U10.6 (V_{SS}), U10.12 (A1), U10.29 (EP), U11.6 (V_{SS}), U11.11 (A0), U11.29 (EP), U12.6 (V_{SS}), U12.29 (EP)
LED_CLK: J1.2, J3.2, J5.2, J7.2, J9.2, J11.2, J13.2, J15.2, J17.2, J19.2, J21.2, J23.2, J25.2, J27.2, J29.2, J31.2, J33.2, J35.2, J37.2, J39.2, J41.2, J43.2, J45.2, J47.2, J49.2, J51.2, J53.2, J55.2, J57.2, J59.2, J61.2, J63.2, J65.2, J67.2, J69.2, J71.2, J73.2, J75.2, J77.2, J79.2
LED_LAT: J1.3, J3.3, J5.3, J7.3, J9.3, J11.3, J13.3, J15.3, J17.3, J19.3, J21.3, J23.3, J25.3, J27.3, J29.3, J31.3, J33.3, J35.3, J37.3, J39.3, J41.3, J43.3, J45.3, J47.3, J49.3, J51.3, J53.3, J55.3, J57.3, J59.3, J61.3, J63.3, J65.3, J67.3, J69.3, J71.3, J73.3, J75.3, J77.3, J79.3
LED_OE: J1.4, J3.4, J5.4, J7.4, J9.4, J11.4, J13.4, J15.4, J17.4, J19.4, J21.4, J23.4, J25.4, J27.4, J29.4, J31.4, J33.4, J35.4, J37.4, J39.4, J41.4, J43.4, J45.4, J47.4, J49.4, J51.4, J53.4, J55.4, J57.4, J59.4, J61.4, J63.4, J65.4, J67.4, J69.4, J71.4, J73.4, J75.4, J77.4, J79.4
unnamed: J2.1, J3.1
unnamed: J4.1, J5.1
unnamed: J6.1, J7.1
unnamed: J8.1, J9.1
unnamed: J10.1, J11.1
unnamed: J12.1, J13.1
unnamed: J14.1, J15.1
unnamed: J16.1, J17.1
unnamed: J18.1, J19.1
unnamed: J22.1, J23.1
unnamed: J24.1, J25.1
unnamed: J26.1, J27.1
unnamed: J28.1, J29.1
unnamed: J30.1, J31.1
unnamed: J32.1, J33.1
unnamed: J34.1, J35.1
unnamed: J36.1, J37.1
unnamed: J38.1, J39.1
unnamed: J42.1, J43.1
unnamed: J44.1, J45.1
unnamed: J46.1, J47.1
unnamed: J48.1, J49.1
unnamed: J50.1, J51.1
unnamed: J52.1, J53.1
unnamed: J54.1, J55.1
unnamed: J56.1, J57.1
unnamed: J58.1, J59.1
unnamed: J62.1, J63.1
unnamed: J64.1, J65.1
unnamed: J66.1, J67.1
unnamed: J68.1, J69.1
unnamed: J70.1, J71.1
unnamed: J72.1, J73.1
unnamed: J74.1, J75.1
unnamed: J76.1, J77.1
unnamed: J78.1, J79.1
